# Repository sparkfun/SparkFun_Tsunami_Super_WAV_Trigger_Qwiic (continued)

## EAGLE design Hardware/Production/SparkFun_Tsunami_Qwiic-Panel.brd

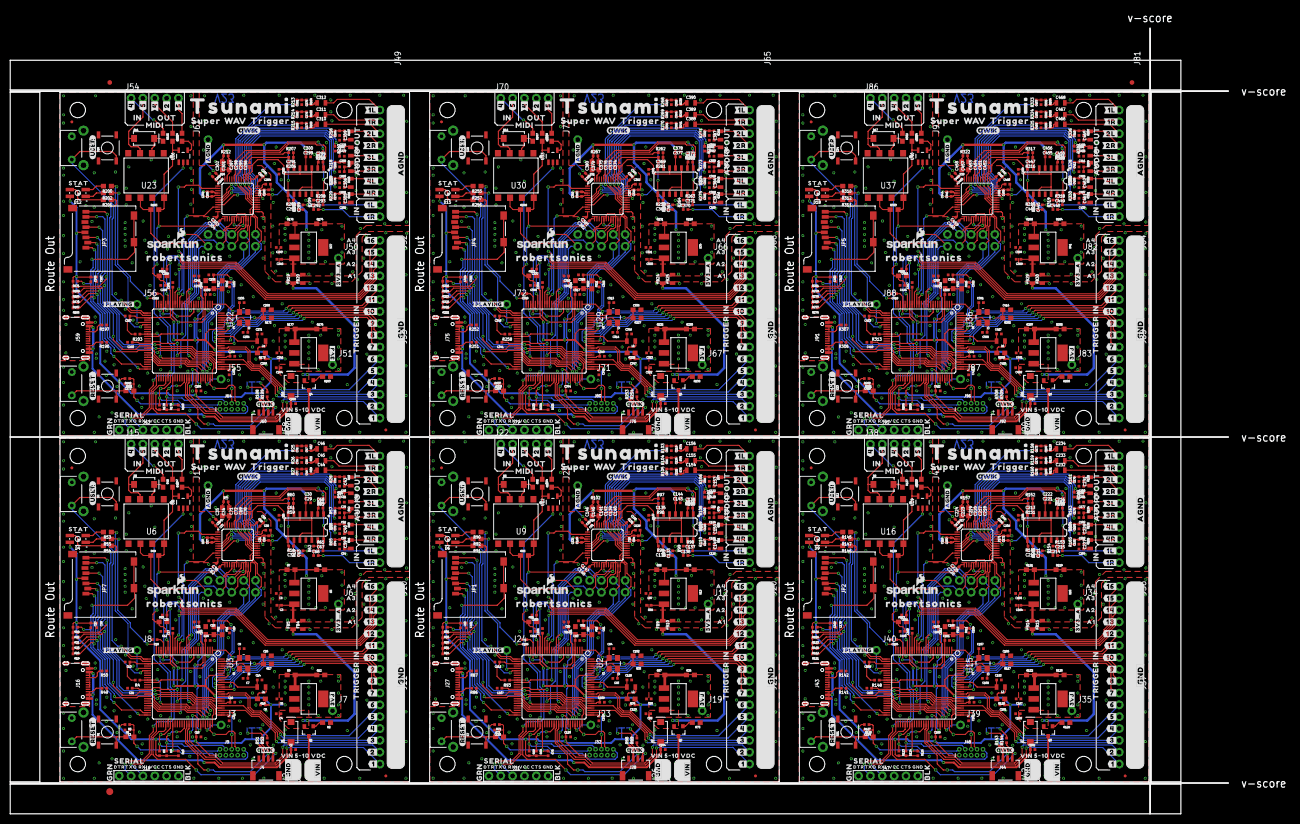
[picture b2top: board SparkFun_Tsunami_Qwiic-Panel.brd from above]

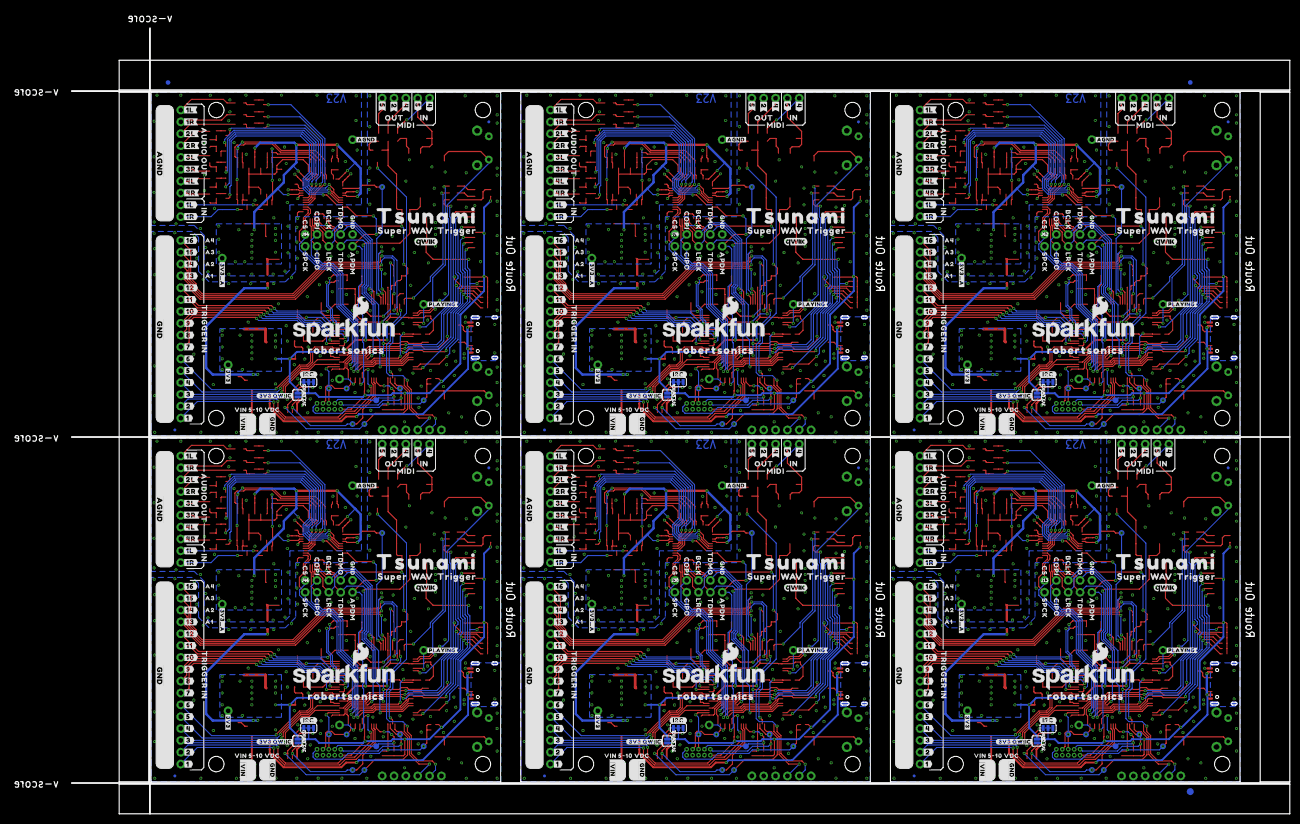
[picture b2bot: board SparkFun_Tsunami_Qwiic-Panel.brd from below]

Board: 2 copper layers, 261.1 x 168.4 mm, 1956 parts (507 on the bottom side), 828 nets.

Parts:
3V3_QWIIC, 3V3_QWIIC1, 3V3_QWIIC2, 3V3_QWIIC3, 3V3_QWIIC4, 3V3_QWIIC5: SMT-JUMPER_2_NO_SILK
C1, C116, C194, C272, C350, C428: 10nF; 0402-TIGHT
C2, C5, C6, C11, C27, C85, C87, C89, C90, C104, C163, C165, C167, C168, C182, C241, C243, C245, C246, C260, C319, C321, C323, C324, C338, C397, C399, C401, C402, C416: 10uF; 0402-TIGHT
C3, C4, C8, C10, C12, C13, C15, C16, C17, C18, C19, C21, C22, C23, C24, C26, C28, C29, C31, C36, C37, C47, C48, C49, C50, C51, C52, C53, C54, C55, C56, C57, C59, C73, C74, C75, C76, C77, C78, C79, C80, C81, C82, C83, C86, C88, C91, C93, C95, C96, C97, C98, C99, C100, C101, C103, C105, C106, C107, C108, C109, C110, C111, C112, C113, C114, C117, C118, C119, C120, C121, C122, C123, C124, C125, C126, C127, C128, C129, C131, C143, C147, C159, C160, C161, C164, C166, C169, C171, C173, C174, C175, C176, C177, C178, C179, C181, C183, C184, C185, C186, C187, C188, C189, C190, C191, C192, C195, C196, C197, C198, C199, C200, C201, C202, C203, C204, C205, C206, C207, C209, C221, C225, C237, C238, C239, C242, C244, C247, C249, C251, C252, C253, C254, C255, C256, C257, C259, C261, C262, C263, C264, C265, C266, C267, C268, C269, C270, C273, C274, C275, C276, C277, C278, C279, C280, C281, C282, C283, C284, C285, C287, C299, C303, C315, C316, C317, C320, C322, C325, C327, C329, C330, C331, C332, C333, C334, C335, C337, C339, C340, C341, C342, C343, C344, C345, C346, C347, C348, C351, C352, C353, C354, C355, C356, C357, C358, C359, C360, C361, C362, C363, C365, C377, C381, C393, C394, C395, C398, C400, C403, C405, C407, C408, C409, C410, C411, C412, C413, C415, C417, C418, C419, C420, C421, C422, C423, C424, C425, C426, C429, C430, C431, C432, C433, C434, C435, C436, C437, C438, C439, C440, C441, C443, C455, C459: 0.1uF; 0402-TIGHT
C7, C9, C64, C65, C157, C158, C235, C236, C313, C314, C391, C392: 12pF; 0402-TIGHT
C14, C115, C193, C271, C349, C427: 4.7uF; 0402-TIGHT
C20, C102, C180, C258, C336, C414: 10pF; 0603
C25, C84, C162, C240, C318, C396: 2.2uF; 0603
C30, C32, C38, C58, C60, C62, C63, C66, C69, C70, C71, C72, C92, C94, C130, C132, C133, C136, C139, C140, C141, C142, C144, C148, C170, C172, C208, C210, C211, C214, C217, C218, C219, C220, C222, C226, C248, C250, C286, C288, C289, C292, C295, C296, C297, C298, C300, C304, C326, C328, C364, C366, C367, C370, C373, C374, C375, C376, C378, C382, C404, C406, C442, C444, C445, C448, C451, C452, C453, C454, C456, C460: 1.0uF; 0402-TIGHT
C33, C61, C67, C68, C134, C135, C137, C138, C212, C213, C215, C216, C290, C291, C293, C294, C368, C369, C371, C372, C446, C447, C449, C450: 100pF; 0402-TIGHT
C34, C145, C223, C301, C379, C457: 5.6nF; 0603
C35, C146, C224, C302, C380, C458: 390nF; 0603
C39, C40, C41, C42, C43, C44, C45, C46, C149, C150, C151, C152, C153, C154, C155, C156, C227, C228, C229, C230, C231, C232, C233, C234, C305, C306, C307, C308, C309, C310, C311, C312, C383, C384, C385, C386, C387, C388, C389, C390, C461, C462, C463, C464, C465, C466, C467, C468: 22uF; 0805
D1, D2, D3, D5, D7, D8, D10, D11, D13, D14, D16, D17: 1A/40V/500mV; SMA-DIODE
D4, D6, D9, D12, D15, D18: RGB; P-LCC-4-3
E$1, E$2, E$3, E$4: FIDUCIAL-1X2
E$5, E$6: FIDUCIAL-1.5X3
FB1, FB2, FB3, FB6, FB7, FB8, FB11, FB12, FB13, FB16, FB17, FB18, FB21, FB22, FB23, FB26, FB27, FB28: 470Ω; 0603
FB4, FB5, FB9, FB10, FB14, FB15, FB19, FB20, FB24, FB25, FB29, FB30: 600Ω; 0805
FD1, FD2, FD3, FD4, FD5, FD6, FD7, FD8, FD9, FD10, FD11, FD12, FD13, FD14, FD15, FD16, FD17, FD18, FD19, FD20, FD21, FD22, FD23, FD24: FIDUCIALUFIDUCIAL; FIDUCIAL-MICRO
H1, H2, H3, H4, H5, H6, H7, H8, H9, H10, H11, H12, H13, H14, H15, H16, H17, H18, H19, H20, H21, H22, H23, H24: STAND-OFF
I2C, I2C1, I2C2, I2C3, I2C4, I2C5: SMT-JUMPER_3_2-NC_TRACE_SILK
J1, J25, J41, J57, J73, J89: VDC-IN; 1X02_NO_SILK
J2, J26, J42, J58, J74, J90: GND-IN; 1X02_NO_SILK
J3, J23, J39, J55, J71, J87: DEBUG; 1X01_NO_SILK
J4, J28, J44, J60, J76, J92: QWIIC; JST04_1MM_RA
J5, J14, J33, J49, J65, J81: AUDIO I/O; 2X10_NOSILK
J6, J12, J34, J50, J66, J82: 3.3VA; 1X01_NO_SILK
J7, J19, J35, J51, J67, J83: 3.3V; 1X01_NO_SILK
J8, J24, J40, J56, J72, J88: PLAYING; 1X01_NO_SILK
J9, J32, J48, J64, J80, J96: CORTEX_JTAG_DEBUG_PTH_NS; 2X5-PTH-1.27MM-NO_SILK
J10, J20, J36, J52, J68, J84: TRIG2; 2X8_NOSILK
J11, J21, J37, J53, J69, J85: TRIG1; 2X8_NOSILK
J13, J30, J46, J62, J78, J94: 2X5_NOSILK
J15, J22, J38, J54, J70, J86: MIDI; 1X05_NO_SILK
J16, J27, J43, J59, J75, J91: USB-C; USB-C-16P-4LAYER-ISOLATED
J17, J29, J45, J61, J77, J93: AGND; 1X01_NO_SILK
J18, J31, J47, J63, J79, J95: 6_PIN_SERIAL_TARGET_SIDE_W_SILK
JP1, JP2, JP3, JP4, JP5, JP7: USD-SOCKETNEW; MICRO-SD-SOCKET-PP
L1, L2, L3, L4, L5, L6: 10μH; 0805
LOGO1, LOGO3, LOGO5, LOGO7, LOGO9, LOGO11: QWIIC_LOGO_4MM; QWIIC_4MM
LOGO2, LOGO4, LOGO6, LOGO8, LOGO10, LOGO12: SFE_LOGO_NAME_FLAME.2_INCH; SFE_LOGO_NAME_FLAME_.2
Q1, Q2, Q3, Q4, Q5, Q6: 3.1A/30V/105mΩ; SOT23-3
R1, R71, R126, R181, R236, R291: 33; 0603
R2, R73, R128, R183, R238, R293: 1M; 0603
R3, R4, R18, R23, R31, R32, R72, R93, R115, R116, R127, R148, R170, R171, R182, R203, R225, R226, R237, R258, R280, R281, R292, R313: 10k; 0402-TIGHT
R5, R102, R157, R212, R267, R322: 560Ω; 0402-TIGHT
R6, R9, R10, R13, R19, R20, R21, R22, R24, R29, R30, R68, R69, R70, R111, R112, R113, R114, R123, R124, R125, R166, R167, R168, R169, R178, R179, R180, R221, R222, R223, R224, R233, R234, R235, R276, R277, R278, R279, R288, R289, R290: 100k; 0402-TIGHT
R7, R8, R66, R67, R121, R122, R176, R177, R231, R232, R286, R287: 390; 0603
R11, R12, R35, R36, R119, R120, R174, R175, R229, R230, R284, R285: 240; 0603
R14, R15, R59, R60, R61, R62, R63, R64, R94, R95, R96, R97, R98, R99, R100, R101, R149, R150, R151, R152, R153, R154, R155, R156, R204, R205, R206, R207, R208, R209, R210, R211, R259, R260, R261, R262, R263, R264, R265, R266, R314, R315, R316, R317, R318, R319, R320, R321: 33k; 0402-TIGHT
R16, R34, R118, R173, R228, R283: 2.2; 0603
R17, R33, R117, R172, R227, R282: 5.62k; 0603
R25, R26, R27, R28, R37, R38, R39, R40, R41, R42, R43, R44, R56, R57, R58, R65, R74, R75, R76, R77, R78, R79, R80, R81, R103, R104, R105, R106, R107, R108, R109, R110, R129, R130, R131, R132, R133, R134, R135, R136, R158, R159, R160, R161, R162, R163, R164, R165, R184, R185, R186, R187, R188, R189, R190, R191, R213, R214, R215, R216, R217, R218, R219, R220, R239, R240, R241, R242, R243, R244, R245, R246, R268, R269, R270, R271, R272, R273, R274, R275, R294, R295, R296, R297, R298, R299, R300, R301, R323, R324, R325, R326, R327, R328, R329, R330: 10Ω; 0402-TIGHT
R45, R46, R47, R48, R55, R82, R83, R84, R85, R92, R137, R138, R139, R140, R147, R192, R193, R194, R195, R202, R247, R248, R249, R250, R257, R302, R303, R304, R305, R312: 220; 0603
R49, R50, R86, R87, R141, R142, R196, R197, R251, R252, R306, R307: 5.1k; 0402-TIGHT
R51, R52, R88, R89, R143, R144, R198, R199, R253, R254, R308, R309: 2.2k; 0402-TIGHT
R53, R54, R90, R91, R145, R146, R200, R201, R255, R256, R310, R311: 100; 0603
S1, S7, S11, S15, S19, S23: Reset; TACTILE_SWITCH_SMD_5.2MM
S2, S4, S5, S6, S9, S10, S13, S14, S17, S18, S21, S22: DNP; TACTILE_SWITCH_PTH_RIGHT_ANGLE
S3, S8, S12, S16, S20, S24: User; TACTILE_SWITCH_SMD_5.2MM
TP1, TP14, TP22, TP30, TP38, TP46: I2C_SCK; PAD.03X.05
TP2, TP15, TP23, TP31, TP39, TP47: I2C_SDA; PAD.03X.05
TP3, TP5, TP17, TP25, TP33, TP41: SWDIO/TMS; PAD.03X.05
TP4, TP16, TP24, TP32, TP40, TP48: MCLK; PAD.03X.05
TP6, TP10, TP18, TP26, TP34, TP42: SWCK/TCK; PAD.03X.05
TP7, TP11, TP19, TP27, TP35, TP43: TDO; PAD.03X.05
TP8, TP12, TP20, TP28, TP36, TP44: TDI; PAD.03X.05
TP9, TP13, TP21, TP29, TP37, TP45: NRESET; PAD.03X.05
U1, U5, U13, U14, U20, U21, U27, U28, U34, U35, U41, U42: LM1117; SOT223
U2, U3, U15, U22, U29, U36: ATSAMS70N20A-AN; LQFP100
U4, U11, U18, U25, U32, U39: LMV324; SO14
U6, U9, U16, U23, U30, U37: 6N138M; 8-SMD
U7, U10, U17, U24, U31, U38: ADAU1328; LQFP-48
U8, U12, U19, U26, U33, U40: 74AHC1G125W5-7; SOT23-5
U$1, U$4, U$73, U$193, U$267, U$326, U$400, U$459, U$533, U$592, U$666, U$725: QWIIC_5MM
U$2, U$5, U$268, U$401, U$534, U$667: STAT0
U$3, U$264, U$397, U$530, U$663, U$796: GND_0
U$6, U$42, U$269, U$402, U$535, U$668: #USER#0
U$7, U$90, U$270, U$403, U$536, U$669: #RESET#0
U$8, U$9, U$100, U$101, U$271, U$272, U$404, U$405, U$537, U$538, U$670, U$671: ROBERTSONICS0
U$10, U$115, U$167, U$229, U$275, U$362, U$408, U$495, U$541, U$628, U$674, U$761: #2L#0
U$11, U$114, U$274, U$407, U$540, U$673: #1L#0
U$12, U$109, U$120, U$226, U$273, U$359, U$406, U$492, U$539, U$625, U$672, U$758: #1R#0
U$13, U$125, U$276, U$409, U$542, U$675: #2R#0
U$14, U$126, U$277, U$410, U$543, U$676: #3R#0
U$15, U$127, U$278, U$411, U$544, U$677: #3L#0
U$16, U$128, U$279, U$412, U$545, U$678: #4L#0
U$17, U$129, U$280, U$413, U$546, U$679: #4R#0
U$18, U$217, U$350, U$483, U$616, U$749: #4#3
U$19, U$218, U$351, U$484, U$617, U$750: #2#5
U$20, U$107, U$130, U$201, U$281, U$334, U$414, U$467, U$547, U$600, U$680, U$733: AUDIO_OUT0
U$21, U$46, U$108, U$123, U$131, U$157, U$202, U$207, U$282, U$307, U$335, U$340, U$415, U$440, U$468, U$473, U$548, U$573, U$601, U$606, U$681, U$706, U$734, U$739: IN0
U$22, U$106, U$132, U$200, U$283, U$333, U$416, U$466, U$549, U$599, U$682, U$732: TRIGGER_IN0
U$23, U$85, U$134, U$195, U$285, U$328, U$418, U$461, U$551, U$594, U$684, U$727: #GND#0
U$24, U$135, U$286, U$419, U$552, U$685: #1#0
U$25, U$186, U$319, U$452, U$585, U$718: SERIAL3
U$26, U$60, U$161, U$187, U$311, U$320, U$444, U$453, U$577, U$586, U$710, U$719: SUPER0
U$27, U$99, U$265, U$266, U$398, U$399, U$531, U$532, U$664, U$665, U$797, U$798: VIN_5#10_VDC0
U$28, U$84, U$133, U$194, U$284, U$327, U$417, U$460, U$550, U$593, U$683, U$726: #AGND#0
U$29, U$136, U$287, U$420, U$553, U$686: #2#0
U$30, U$137, U$288, U$421, U$554, U$687: #3#0
U$31, U$56, U$117, U$138, U$159, U$223, U$289, U$309, U$356, U$422, U$442, U$489, U$555, U$575, U$622, U$688, U$708, U$755: #4#0
U$32, U$58, U$118, U$139, U$160, U$224, U$290, U$310, U$357, U$423, U$443, U$490, U$556, U$576, U$623, U$689, U$709, U$756: #5#0
U$33, U$140, U$291, U$424, U$557, U$690: #6#0
U$34, U$142, U$292, U$425, U$558, U$691: #7#0
U$35, U$143, U$293, U$426, U$559, U$692: #8#0
U$36, U$144, U$294, U$427, U$560, U$693: #9#0
U$37, U$145, U$295, U$428, U$561, U$694: #10#0
U$38, U$146, U$296, U$429, U$562, U$695: #11#0
U$39, U$147, U$297, U$430, U$563, U$696: #12#0
U$40, U$263, U$396, U$529, U$662, U$795: #PLAYING#30
U$41, U$112, U$211, U$214, U$344, U$347, U$477, U$480, U$610, U$613, U$743, U$746: #3V3#0
U$43, U$148, U$298, U$431, U$564, U$697: #13#0
U$44, U$212, U$345, U$478, U$611, U$744: #3V3_A#0
U$45, U$122, U$156, U$206, U$306, U$339, U$439, U$472, U$572, U$605, U$705, U$738: MIDI0
U$47, U$124, U$158, U$208, U$308, U$341, U$441, U$474, U$574, U$607, U$707, U$740: OUT0
U$48, U$149, U$299, U$432, U$565, U$698: #14#0
U$49, U$150, U$300, U$433, U$566, U$699: #15#0
U$50, U$151, U$301, U$434, U$567, U$700: #16#0
U$51, U$152, U$302, U$435, U$568, U$701: A10
U$52, U$153, U$303, U$436, U$569, U$702: A20
U$53, U$154, U$304, U$437, U$570, U$703: A30
U$54, U$155, U$305, U$438, U$571, U$704: A40
U$55, U$220, U$353, U$486, U$619, U$752: #5#6
U$57, U$221, U$354, U$487, U$620, U$753: #2#6
U$59, U$222, U$355, U$488, U$621, U$754: #4#6
U$61, U$110, U$184, U$203, U$317, U$336, U$450, U$469, U$583, U$602, U$716, U$735: #GND#1
U$62, U$68, U$179, U$188, U$312, U$321, U$445, U$454, U$578, U$587, U$711, U$720: TRIGGER0
U$63, U$69, U$180, U$189, U$313, U$322, U$446, U$455, U$579, U$588, U$712, U$721: TSUNAMI0
U$64, U$70, U$181, U$190, U$314, U$323, U$447, U$456, U$580, U$589, U$713, U$722: W0
U$65, U$71, U$182, U$191, U$315, U$324, U$448, U$457, U$581, U$590, U$714, U$723: A0
U$66, U$72, U$183, U$192, U$316, U$325, U$449, U$458, U$582, U$591, U$715, U$724: V0
U$67, U$111, U$185, U$204, U$318, U$337, U$451, U$470, U$584, U$603, U$717, U$736: #VIN#2
U$74, U$235, U$368, U$501, U$634, U$767: #16#5
U$75, U$236, U$369, U$502, U$635, U$768: #15#17
U$76, U$237, U$370, U$503, U$636, U$769: #14#17
U$77, U$238, U$371, U$504, U$637, U$770: #13#17
U$78, U$239, U$372, U$505, U$638, U$771: #12#17
U$79, U$240, U$373, U$506, U$639, U$772: #11#17
U$80, U$241, U$374, U$507, U$640, U$773: #10#17
U$81, U$242, U$375, U$508, U$641, U$774: #9#17
U$82, U$243, U$376, U$509, U$642, U$775: #8#17
U$83, U$244, U$377, U$510, U$643, U$776: #7#17
U$86, U$251, U$384, U$517, U$650, U$783: CS17
U$87, U$252, U$385, U$518, U$651, U$784: BCLK19
U$88, U$253, U$386, U$519, U$652, U$785: COPI18
U$89, U$254, U$387, U$520, U$653, U$786: TDMO20
U$91, U$255, U$388, U$521, U$654, U$787: SPCK22
U$92, U$256, U$389, U$522, U$655, U$788: TDMI25
U$93, U$257, U$390, U$523, U$656, U$789: LRCK24
U$94, U$258, U$391, U$524, U$657, U$790: CIPO23
U$95, U$259, U$392, U$525, U$658, U$791: APDM26
U$96, U$260, U$393, U$526, U$659, U$792: #AGND#27
U$97, U$261, U$394, U$527, U$660, U$793: #AGND#28
U$98, U$262, U$395, U$528, U$661, U$794: #PLAYING#29
U$102, U$196, U$329, U$462, U$595, U$728: A117
U$103, U$197, U$330, U$463, U$596, U$729: A2118
U$104, U$198, U$331, U$464, U$597, U$730: A32119
U$105, U$199, U$332, U$465, U$598, U$731: A432120
U$113, U$205, U$338, U$471, U$604, U$737: #I2C#6
U$116, U$215, U$348, U$481, U$614, U$747: #1L#3
U$119, U$225, U$358, U$491, U$624, U$757: #1L#6
U$121, U$227, U$360, U$493, U$626, U$759: #1R#2
U$141, U$209, U$342, U$475, U$608, U$741: SFE_LOGO_NAME_FLAME_.1
U$162, U$213, U$346, U$479, U$612, U$745: #3V3_A#4
U$163, U$210, U$343, U$476, U$609, U$742: #3V3_QWIIC#0
U$164, U$216, U$349, U$482, U$615, U$748: #1R#3
U$165, U$219, U$352, U$485, U$618, U$751: #5#5
U$166, U$228, U$361, U$494, U$627, U$760: #1L#2
U$168, U$230, U$363, U$496, U$629, U$762: #2R#3
U$169, U$231, U$364, U$497, U$630, U$763: #3L#3
U$170, U$232, U$365, U$498, U$631, U$764: #3R#4
U$171, U$233, U$366, U$499, U$632, U$765: #4L#4
U$172, U$234, U$367, U$500, U$633, U$766: #4R#5
U$173, U$245, U$378, U$511, U$644, U$777: #6#17
U$174, U$246, U$379, U$512, U$645, U$778: #5#17
U$175, U$247, U$380, U$513, U$646, U$779: #4#17
U$176, U$248, U$381, U$514, U$647, U$780: #3#17
U$177, U$249, U$382, U$515, U$648, U$781: #2#17
U$178, U$250, U$383, U$516, U$649, U$782: #1#17
Y1, Y2, Y3, Y4, Y5, Y6: 11.2896 MHz; CRYSTAL-SMD-3.2X2.5MM_GEYER_12.60421

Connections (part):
1: D5.C, R82.2, U9.2
2: D8.C, R137.2, U16.2
3: D11.C, R192.2, U23.2
3.3V: 3V3_QWIIC.1, C6.1, C8.1, C10.1, C11.1, C12.1, C13.1, C15.1, C16.1, C27.1, C28.1, C36.1, C62.1, D4.4, FB3.1, I2C.2, J7.1, J9.1, JP7.VCC, R3.2, R4.2, R6.2, R9.2, R10.2, R12.2, R16.1, R18.2, R19.2, R20.2, R21.2, R22.2, R23.2, R47.2, R48.2, U1.2, U1.4, U3.5, U3.19, U3.28, U3.68, U3.81, U3.93, U6.8, U7.13, U8.5
3.3V1: 3V3_QWIIC1.1, C85.1, C89.1, C90.1, C101.1, C109.1, C110.1, C111.1, C112.1, C113.1, C114.1, C147.1, C148.1, D6.4, FB8.1, I2C1.2, J19.1, J32.1, JP1.VCC, R13.2, R24.2, R29.2, R30.2, R31.2, R32.2, R34.1, R36.2, R68.2, R69.2, R70.2, R72.2, R83.2, R84.2, R93.2, U2.5, U2.19, U2.28, U2.68, U2.81, U2.93, U9.8, U10.13, U12.5, U14.2, U14.4
3.3V2: 3V3_QWIIC2.1, C163.1, C167.1, C168.1, C179.1, C187.1, C188.1, C189.1, C190.1, C191.1, C192.1, C225.1, C226.1, D9.4, FB13.1, I2C2.2, J35.1, J48.1, JP2.VCC, R111.2, R112.2, R113.2, R114.2, R115.2, R116.2, R118.1, R120.2, R123.2, R124.2, R125.2, R127.2, R138.2, R139.2, R148.2, U15.5, U15.19, U15.28, U15.68, U15.81, U15.93, U16.8, U17.13, U19.5, U21.2, U21.4
3.3V3: 3V3_QWIIC3.1, C241.1, C245.1, C246.1, C257.1, C265.1, C266.1, C267.1, C268.1, C269.1, C270.1, C303.1, C304.1, D12.4, FB18.1, I2C3.2, J51.1, J64.1, JP3.VCC, R166.2, R167.2, R168.2, R169.2, R170.2, R171.2, R173.1, R175.2, R178.2, R179.2, R180.2, R182.2, R193.2, R194.2, R203.2, U22.5, U22.19, U22.28, U22.68, U22.81, U22.93, U23.8, U24.13, U26.5, U28.2, U28.4
3.3V4: 3V3_QWIIC4.1, C319.1, C323.1, C324.1, C335.1, C343.1, C344.1, C345.1, C346.1, C347.1, C348.1, C381.1, C382.1, D15.4, FB23.1, I2C4.2, J67.1, J80.1, JP4.VCC, R221.2, R222.2, R223.2, R224.2, R225.2, R226.2, R228.1, R230.2, R233.2, R234.2, R235.2, R237.2, R248.2, R249.2, R258.2, U29.5, U29.19, U29.28, U29.68, U29.81, U29.93, U30.8, U31.13, U33.5, U35.2, U35.4
3.3V5: 3V3_QWIIC5.1, C397.1, C401.1, C402.1, C413.1, C421.1, C422.1, C423.1, C424.1, C425.1, C426.1, C459.1, C460.1, D18.4, FB28.1, I2C5.2, J83.1, J96.1, JP5.VCC, R276.2, R277.2, R278.2, R279.2, R280.2, R281.2, R283.1, R285.2, R288.2, R289.2, R290.2, R292.2, R303.2, R304.2, R313.2, U36.5, U36.19, U36.28, U36.68, U36.81, U36.93, U37.8, U38.13, U40.5, U42.2, U42.4
4: D14.C, R247.2, U30.2
5: D17.C, R302.2, U37.2
56: D3.C, R45.2, U6.2
ADC1LN: C69.1, U7.40
ADC1LN1: C139.1, U10.40
ADC1LN2: C217.1, U17.40
ADC1LN3: C295.1, U24.40
ADC1LN4: C373.1, U31.40
ADC1LN5: C451.1, U38.40
ADC1LP: C70.1, U7.39
ADC1LP1: C140.1, U10.39
ADC1LP2: C218.1, U17.39
ADC1LP3: C296.1, U24.39
ADC1LP4: C374.1, U31.39
ADC1LP5: C452.1, U38.39
ADC2LN: C71.1, U7.44
ADC2LN1: C141.1, U10.44
ADC2LN2: C219.1, U17.44
ADC2LN3: C297.1, U24.44
ADC2LN4: C375.1, U31.44
ADC2LN5: C453.1, U38.44
ADC2LP: C72.1, U7.43
ADC2LP1: C142.1, U10.43
ADC2LP2: C220.1, U17.43
ADC2LP3: C298.1, U24.43
ADC2LP4: C376.1, U31.43
ADC2LP5: C454.1, U38.43
AGND: C3.2, C5.2, C29.2, C30.2, C31.2, C32.2, C37.2, C38.2, C47.2, C48.2, C49.2, C50.2, C51.2, C52.2, C53.2, C54.2, C55.2, C56.2, C57.2, C58.2, C59.2, C60.2, C73.1, C74.1, C75.1, C76.1, C77.1, C78.1, C79.1, C80.1, FB4.2, J14.2, J14.4, J14.6, J14.8, J14.10, J14.12, J14.14, J14.16, J14.18, J14.20, J17.1, R7.1, U4.11, U7.1, U7.4, U7.32, U7.34, U7.36
AGND1: C86.2, C87.2, C91.2, C92.2, C93.2, C94.2, C95.1, C96.1, C97.1, C98.1, C99.1, C100.1, C117.1, C118.1, C119.2, C120.2, C121.2, C122.2, C123.2, C124.2, C125.2, C126.2, C127.2, C128.2, C129.2, C130.2, C131.2, C132.2, C143.2, C144.2, FB10.2, J5.2, J5.4, J5.6, J5.8, J5.10, J5.12, J5.14, J5.16, J5.18, J5.20, J29.1, R66.1, U10.1, U10.4, U10.32, U10.34, U10.36, U11.11
AGND2: C164.2, C165.2, C169.2, C170.2, C171.2, C172.2, C173.1, C174.1, C175.1, C176.1, C177.1, C178.1, C195.1, C196.1, C197.2, C198.2, C199.2, C200.2, C201.2, C202.2, C203.2, C204.2, C205.2, C206.2, C207.2, C208.2, C209.2, C210.2, C221.2, C222.2, FB15.2, J33.2, J33.4, J33.6, J33.8, J33.10, J33.12, J33.14, J33.16, J33.18, J33.20, J45.1, R121.1, U17.1, U17.4, U17.32, U17.34, U17.36, U18.11
AGND3: C242.2, C243.2, C247.2, C248.2, C249.2, C250.2, C251.1, C252.1, C253.1, C254.1, C255.1, C256.1, C273.1, C274.1, C275.2, C276.2, C277.2, C278.2, C279.2, C280.2, C281.2, C282.2, C283.2, C284.2, C285.2, C286.2, C287.2, C288.2, C299.2, C300.2, FB20.2, J49.2, J49.4, J49.6, J49.8, J49.10, J49.12, J49.14, J49.16, J49.18, J49.20, J61.1, R176.1, U24.1, U24.4, U24.32, U24.34, U24.36, U25.11
AGND4: C320.2, C321.2, C325.2, C326.2, C327.2, C328.2, C329.1, C330.1, C331.1, C332.1, C333.1, C334.1, C351.1, C352.1, C353.2, C354.2, C355.2, C356.2, C357.2, C358.2, C359.2, C360.2, C361.2, C362.2, C363.2, C364.2, C365.2, C366.2, C377.2, C378.2, FB25.2, J65.2, J65.4, J65.6, J65.8, J65.10, J65.12, J65.14, J65.16, J65.18, J65.20, J77.1, R231.1, U31.1, U31.4, U31.32, U31.34, U31.36, U32.11
AGND5: C398.2, C399.2, C403.2, C404.2, C405.2, C406.2, C407.1, C408.1, C409.1, C410.1, C411.1, C412.1, C429.1, C430.1, C431.2, C432.2, C433.2, C434.2, C435.2, C436.2, C437.2, C438.2, C439.2, C440.2, C441.2, C442.2, C443.2, C444.2, C455.2, C456.2, FB30.2, J81.2, J81.4, J81.6, J81.8, J81.10, J81.12, J81.14, J81.16, J81.18, J81.20, J93.1, R286.1, U38.1, U38.4, U38.32, U38.34, U38.36, U39.11
AIN1L: C63.2, J14.17
AIN1L1: C133.2, J5.17
AIN1L2: C211.2, J33.17
AIN1L3: C289.2, J49.17
AIN1L4: C367.2, J65.17
AIN1L5: C445.2, J81.17
AIN1R: C66.2, J14.19
AIN1R1: C136.2, J5.19
AIN1R2: C214.2, J33.19
AIN1R3: C292.2, J49.19
AIN1R4: C370.2, J65.19
AIN1R5: C448.2, J81.19
AOUT1L: C46.1, C47.1, R37.2
AOUT1L1: C119.1, C156.1, R74.2
AOUT1L2: C197.1, C234.1, R129.2
AOUT1L3: C275.1, C312.1, R184.2
AOUT1L4: C353.1, C390.1, R239.2
AOUT1L5: C431.1, C468.1, R294.2
AOUT1R: C45.1, C48.1, R38.2
AOUT1R1: C120.1, C155.1, R75.2
AOUT1R2: C198.1, C233.1, R130.2
AOUT1R3: C276.1, C311.1, R185.2
AOUT1R4: C354.1, C389.1, R240.2
AOUT1R5: C432.1, C467.1, R295.2
AOUT2L: C44.2, J14.5
AOUT2L1: C154.2, J5.5
AOUT2L2: C232.2, J33.5
AOUT2L3: C310.2, J49.5
AOUT2L4: C388.2, J65.5
AOUT2L5: C466.2, J81.5
AOUT2R: C43.1, C50.1, R40.2
AOUT2R1: C122.1, C153.1, R77.2
AOUT2R2: C200.1, C231.1, R132.2
AOUT2R3: C278.1, C309.1, R187.2
AOUT2R4: C356.1, C387.1, R242.2
AOUT2R5: C434.1, C465.1, R297.2
AOUT3L: C42.2, J14.9
AOUT3L1: C152.2, J5.9
AOUT3L2: C230.2, J33.9
AOUT3L3: C308.2, J49.9
AOUT3L4: C386.2, J65.9
AOUT3L5: C464.2, J81.9
AOUT3R: C41.1, C52.1, R42.2
AOUT3R1: C124.1, C151.1, R79.2
AOUT3R2: C202.1, C229.1, R134.2
AOUT3R3: C280.1, C307.1, R189.2
AOUT3R4: C358.1, C385.1, R244.2
AOUT3R5: C436.1, C463.1, R299.2
AOUT4L: C40.1, C53.1, R43.2
AOUT4L1: C125.1, C150.1, R80.2
AOUT4L2: C203.1, C228.1, R135.2
AOUT4L3: C281.1, C306.1, R190.2
AOUT4L4: C359.1, C384.1, R245.2
AOUT4L5: C437.1, C462.1, R300.2
AOUT4R: C39.1, C54.1, R44.2
AOUT4R1: C126.1, C149.1, R81.2
AOUT4R2: C204.1, C227.1, R136.2
AOUT4R3: C282.1, C305.1, R191.2
AOUT4R4: C360.1, C383.1, R246.2
AOUT4R5: C438.1, C461.1, R301.2
APDN: J13.9, U3.70, U7.10
APDN1: J30.9, U2.70, U10.10
APDN2: J46.9, U15.70, U17.10
APDN3: J62.9, U22.70, U24.10
APDN4: J78.9, U29.70, U31.10
APDN5: J94.9, U36.70, U38.10
BCLK: J13.6, U3.11, U7.17, U7.21
BCLK1: J30.6, U2.11, U10.17, U10.21
BCLK2: J46.6, U15.11, U17.17, U17.21
BCLK3: J62.6, U22.11, U24.17, U24.21
BCLK4: J78.6, U29.11, U31.17, U31.21
BCLK5: J94.6, U36.11, U38.17, U38.21
BLUE_LED: R54.1, U3.31
BLUE_LED1: R91.1, U2.31
BLUE_LED2: R146.1, U15.31
BLUE_LED3: R201.1, U22.31
BLUE_LED4: R256.1, U29.31
BLUE_LED5: R311.1, U36.31
CC1: J16.A5, R50.2
CC2: J16.B5, R49.2
CC3: J27.B5, R86.2
CC4: J27.A5, R87.2
CC5: J43.B5, R141.2
CC6: J43.A5, R142.2
CC7: J59.B5, R196.2
CC8: J59.A5, R197.2
CC9: J75.B5, R251.2
CC10: J75.A5, R252.2
CC11: J91.B5, R306.2
CC12: J91.A5, R307.2
CM_1.5V: C55.1, U4.3, U4.5, U4.10, U4.12, U7.38
CM_1.5V1: C127.1, U10.38, U11.3, U11.5, U11.10, U11.12
CM_1.5V2: C205.1, U17.38, U18.3, U18.5, U18.10, U18.12
CM_1.5V3: C283.1, U24.38, U25.3, U25.5, U25.10, U25.12
CM_1.5V4: C361.1, U31.38, U32.3, U32.5, U32.10, U32.12
CM_1.5V5: C439.1, U38.38, U39.3, U39.5, U39.10, U39.12
DBUG: J3.1, U3.72
DBUG1: J23.1, U2.72
DBUG2: J39.1, U15.72
DBUG3: J55.1, U22.72
DBUG4: J71.1, U29.72
DBUG5: J87.1, U36.72
DGND: C1.2, C2.2, C4.2, C6.2, C7.2, C8.2, C9.2, C10.2, C11.2, C12.2, C13.2, C14.2, C15.2, C16.2, C17.2, C18.2, C19.2, C20.2, C21.2, C22.2, C23.2, C24.2, C25.2, C26.2, C27.2, C28.2, C36.2, C62.2, FB4.1, J2.1, J2.2, J4.1, J9.3, J9.5, J9.9, J10.2, J10.4, J10.6, J10.8, J10.10, J10.12, J10.14, J10.16, J11.2, J11.4, J11.6, J11.8, J11.10, J11.12, J11.14, J11.16, J13.10, J15.4, J16.GND, J16.GND2, J18.6, JP7.GND, JP7.GND1, JP7.GND3, R2.1, R8.1, R17.1, R49.1, R50.1, S1.1, S2.1, S3.1, S4.1, U3.3, U3.6, U3.7, U3.8, U3.10, U3.29, U3.67, U6.5, U7.12, U7.25, U8.1, U8.3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
DGND1: C64.2, C65.2, C81.2, C82.2, C83.2, C84.2, C85.2, C88.2, C89.2, C90.2, C101.2, C102.2, C103.2, C104.2, C105.2, C106.2, C107.2, C108.2, C109.2, C110.2, C111.2, C112.2, C113.2, C114.2, C115.2, C116.2, C147.2, C148.2, FB10.1, J20.2, J20.4, J20.6, J20.8, J20.10, J20.12, J20.14, J20.16, J21.2, J21.4, J21.6, J21.8, J21.10, J21.12, J21.14, J21.16, J22.4, J26.1, J26.2, J27.GND, J27.GND2, J28.1, J30.10, J31.6, J32.3, J32.5, J32.9, JP1.GND, JP1.GND1, JP1.GND3, R33.1, R67.1, R73.1, R86.1, R87.1, S5.1, S6.1, S7.1, S8.1, U2.3, U2.6, U2.7, U2.8, U2.10, U2.29, U2.67, U9.5, U10.12, U10.25, U12.1, U12.3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
DGND2: C157.2, C158.2, C159.2, C160.2, C161.2, C162.2, C163.2, C166.2, C167.2, C168.2, C179.2, C180.2, C181.2, C182.2, C183.2, C184.2, C185.2, C186.2, C187.2, C188.2, C189.2, C190.2, C191.2, C192.2, C193.2, C194.2, C225.2, C226.2, FB15.1, J36.2, J36.4, J36.6, J36.8, J36.10, J36.12, J36.14, J36.16, J37.2, J37.4, J37.6, J37.8, J37.10, J37.12, J37.14, J37.16, J38.4, J42.1, J42.2, J43.GND, J43.GND2, J44.1, J46.10, J47.6, J48.3, J48.5, J48.9, JP2.GND, JP2.GND1, JP2.GND3, R117.1, R122.1, R128.1, R141.1, R142.1, S9.1, S10.1, S11.1, S12.1, U15.3, U15.6, U15.7, U15.8, U15.10, U15.29, U15.67, U16.5, U17.12, U17.25, U19.1, U19.3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
DGND3: C235.2, C236.2, C237.2, C238.2, C239.2, C240.2, C241.2, C244.2, C245.2, C246.2, C257.2, C258.2, C259.2, C260.2, C261.2, C262.2, C263.2, C264.2, C265.2, C266.2, C267.2, C268.2, C269.2, C270.2, C271.2, C272.2, C303.2, C304.2, FB20.1, J52.2, J52.4, J52.6, J52.8, J52.10, J52.12, J52.14, J52.16, J53.2, J53.4, J53.6, J53.8, J53.10, J53.12, J53.14, J53.16, J54.4, J58.1, J58.2, J59.GND, J59.GND2, J60.1, J62.10, J63.6, J64.3, J64.5, J64.9, JP3.GND, JP3.GND1, JP3.GND3, R172.1, R177.1, R183.1, R196.1, R197.1, S13.1, S14.1, S15.1, S16.1, U22.3, U22.6, U22.7, U22.8, U22.10, U22.29, U22.67, U23.5, U24.12, U24.25, U26.1, U26.3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
DGND4: C313.2, C314.2, C315.2, C316.2, C317.2, C318.2, C319.2, C322.2, C323.2, C324.2, C335.2, C336.2, C337.2, C338.2, C339.2, C340.2, C341.2, C342.2, C343.2, C344.2, C345.2, C346.2, C347.2, C348.2, C349.2, C350.2, C381.2, C382.2, FB25.1, J68.2, J68.4, J68.6, J68.8, J68.10, J68.12, J68.14, J68.16, J69.2, J69.4, J69.6, J69.8, J69.10, J69.12, J69.14, J69.16, J70.4, J74.1, J74.2, J75.GND, J75.GND2, J76.1, J78.10, J79.6, J80.3, J80.5, J80.9, JP4.GND, JP4.GND1, JP4.GND3, R227.1, R232.1, R238.1, R251.1, R252.1, S17.1, S18.1, S19.1, S20.1, U29.3, U29.6, U29.7, U29.8, U29.10, U29.29, U29.67, U30.5, U31.12, U31.25, U33.1, U33.3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
DGND5: C391.2, C392.2, C393.2, C394.2, C395.2, C396.2, C397.2, C400.2, C401.2, C402.2, C413.2, C414.2, C415.2, C416.2, C417.2, C418.2, C419.2, C420.2, C421.2, C422.2, C423.2, C424.2, C425.2, C426.2, C427.2, C428.2, C459.2, C460.2, FB30.1, J84.2, J84.4, J84.6, J84.8, J84.10, J84.12, J84.14, J84.16, J85.2, J85.4, J85.6, J85.8, J85.10, J85.12, J85.14, J85.16, J86.4, J90.1, J90.2, J91.GND, J91.GND2, J92.1, J94.10, J95.6, J96.3, J96.5, J96.9, JP5.GND, JP5.GND1, JP5.GND3, R282.1, R287.1, R293.1, R306.1, R307.1, S21.1, S22.1, S23.1, S24.1, U36.3, U36.6, U36.7, U36.8, U36.10, U36.29, U36.67, U37.5, U38.12, U38.25, U40.1, U40.3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
GREEN_LED: R53.1, U3.27
GREEN_LED1: R90.1, U2.27
GREEN_LED2: R145.1, U15.27
GREEN_LED3: R200.1, U22.27
GREEN_LED4: R255.1, U29.27
GREEN_LED5: R310.1, U36.27
I2C_SCK: J4.4, R52.1, TP1.1, U3.55
I2C_SCK1: J28.4, R89.1, TP14.1, U2.55
I2C_SCK2: J44.4, R144.1, TP22.1, U15.55
I2C_SCK3: J60.4, R199.1, TP30.1, U22.55
I2C_SCK4: J76.4, R254.1, TP38.1, U29.55
I2C_SCK5: J92.4, R309.1, TP46.1, U36.55
I2C_SDA: J4.3, R51.1, TP2.1, U3.64
I2C_SDA1: J28.3, R88.1, TP15.1, U2.64
I2C_SDA2: J44.3, R143.1, TP23.1, U15.64
I2C_SDA3: J60.3, R198.1, TP31.1, U22.64
I2C_SDA4: J76.3, R253.1, TP39.1, U29.64
I2C_SDA5: J92.3, R308.1, TP47.1, U36.64
LF: C34.1, C35.1, U7.47
LF1: C145.1, C146.1, U10.47
LF2: C223.1, C224.1, U17.47
LF3: C301.1, C302.1, U24.47
LF4: C379.1, C380.1, U31.47
LF5: C457.1, C458.1, U38.47
LRCK: J13.5, U3.12, U7.18, U7.22
LRCK1: J30.5, U2.12, U10.18, U10.22
LRCK2: J46.5, U15.12, U17.18, U17.22
LRCK3: J62.5, U22.12, U24.18, U24.22
LRCK4: J78.5, U29.12, U31.18, U31.22
LRCK5: J94.5, U36.12, U38.18, U38.22
MCLK: TP4.1, U3.15, U7.2
MCLK1: TP16.1, U2.15, U10.2
MCLK2: TP24.1, U15.15, U17.2
MCLK3: TP32.1, U22.15, U24.2
MCLK4: TP40.1, U29.15, U31.2
MCLK5: TP48.1, U36.15, U38.2
MIDI-IN-PIN1: J22.1, R82.1
MIDI-IN-PIN2: D5.A, J22.2, U9.3
MIDI-IN-PIN3: J38.1, R137.1
MIDI-IN-PIN4: J15.1, R45.1
MIDI-IN-PIN5: D3.A, J15.2, U6.3
MIDI-IN-PIN6: D8.A, J38.2, U16.3
MIDI-IN-PIN7: J54.1, R192.1
MIDI-IN-PIN8: D11.A, J54.2, U23.3
MIDI-IN-PIN9: J70.1, R247.1
MIDI-IN-PIN10: D14.A, J70.2, U30.3
MIDI-IN-PIN11: J86.1, R302.1
MIDI-IN-PIN12: D17.A, J86.2, U37.3
MIDI-OUT-PIN1: J22.3, R84.1
MIDI-OUT-PIN2: J22.5, R85.2
MIDI-OUT-PIN3: J38.3, R139.1
MIDI-OUT-PIN4: J15.3, R47.1
MIDI-OUT-PIN5: J15.5, R46.2
MIDI-OUT-PIN6: J38.5, R140.2
MIDI-OUT-PIN7: J54.3, R194.1
MIDI-OUT-PIN8: J54.5, R195.2
MIDI-OUT-PIN9: J70.3, R249.1
MIDI-OUT-PIN10: J70.5, R250.2
MIDI-OUT-PIN11: J86.3, R304.1
MIDI-OUT-PIN12: J86.5, R305.2
MIN: R48.1, U3.75, U6.6
MIN1: R83.1, U2.75, U9.6
MIN2: R138.1, U15.75, U16.6
MIN3: R193.1, U22.75, U23.6
MIN4: R248.1, U29.75, U30.6
MIN5: R303.1, U36.75, U37.6
MOUT: U3.56, U8.2
MOUT1: U2.56, U12.2
MOUT2: U15.56, U19.2
MOUT3: U22.56, U26.2
MOUT4: U29.56, U33.2
MOUT5: U36.56, U40.2
unnamed: C7.1, U3.98, Y1.1
unnamed: C9.1, U3.99, Y1.3
unnamed: C19.1, FB1.1, U3.96
unnamed: C14.1, L1.2, U3.90
unnamed: C23.1, FB2.1, U3.86
unnamed: C33.2, C69.2, R14.2, R60.1, U4.8
unnamed: I2C.3, R51.2
unnamed: J8.1, U3.30
unnamed: I2C.1, R52.2
unnamed: C65.1, U2.98, Y2.1
unnamed: C34.2, R5.2
unnamed: C63.1, R15.1
unnamed: C64.1, U2.99, Y2.3
unnamed: C61.2, C70.2, R59.2, U4.7
unnamed: C68.2, C72.2, R63.2, U4.1
unnamed: C20.1, R17.2, U3.97
unnamed: C26.1, FB3.2, U3.9
unnamed: C39.2, J14.15
unnamed: C40.2, J14.13
unnamed: C41.2, J14.11
unnamed: C42.1, C51.1, R41.2
unnamed: C43.2, J14.7
unnamed: C75.2, R25.2, R37.1
unnamed: L1.1, R16.2
unnamed: R7.2, R11.1, U5.1
unnamed: R1.1, S1.3, S2.2
unnamed: C74.2, R44.1, R65.2
unnamed: C73.2, R43.1, R58.2
unnamed: R8.2, R12.1, U1.1
unnamed: C80.2, R42.1, R57.2
unnamed: C44.1, C49.1, R39.2
unnamed: C46.2, J14.1
unnamed: C45.2, J14.3
unnamed: 3V3_QWIIC.2, J4.2
unnamed: D4.2, R53.2
unnamed: D4.3, R54.2
unnamed: D4.1, R55.2
unnamed: R46.1, U8.4
unnamed: C81.1, FB6.1, U2.96
unnamed: C82.1, FB7.1, U2.86
unnamed: C102.1, R33.2, U2.97
unnamed: C103.1, FB8.2, U2.9
unnamed: C115.1, L2.2, U2.90
unnamed: L2.1, R34.2
unnamed: C3.1, FB5.2, U5.3
unnamed: R35.1, R66.2, U13.1
unnamed: R36.1, R67.2, U14.1
unnamed: C56.1, U7.35
unnamed: C61.1, R59.1, R60.2, U4.6
unnamed: R71.1, S5.2, S7.3
unnamed: C33.1, R14.1, R15.2, U4.9
unnamed: C79.2, R41.1, R56.2
unnamed: C78.2, R28.2, R40.1
unnamed: C76.2, R26.2, R38.1
unnamed: C77.2, R27.2, R39.1
unnamed: C67.2, C71.2, R61.2, R64.1, U4.14
unnamed: Q2.1, R73.2
unnamed: C66.1, R62.1
unnamed: C68.1, R63.1, R64.2, U4.2
unnamed: C67.1, R61.1, R62.2, U4.13
unnamed: C95.2, R74.1, R103.2
unnamed: C117.2, R81.1, R110.2
unnamed: C118.2, R80.1, R109.2
unnamed: C100.2, R79.1, R108.2
unnamed: C99.2, R78.1, R107.2
unnamed: C98.2, R77.1, R106.2
unnamed: C96.2, R75.1, R104.2
unnamed: C97.2, R76.1, R105.2
unnamed: R85.1, U12.4
unnamed: J24.1, U2.30
unnamed: I2C1.3, R88.2
unnamed: I2C1.1, R89.2
unnamed: D6.2, R90.2
unnamed: D6.3, R91.2
unnamed: Q1.1, R2.2
unnamed: D6.1, R92.2
unnamed: C128.1, U10.35
unnamed: C86.1, FB9.2, U13.3
unnamed: C134.2, C139.2, R94.2, R97.1, U11.8
unnamed: C133.1, R95.1
unnamed: C135.1, R96.1, R97.2, U11.6
unnamed: C134.1, R94.1, R95.2, U11.9
unnamed: C137.2, C141.2, R98.2, R101.1, U11.14
unnamed: C136.1, R99.1
unnamed: C138.1, R100.1, R101.2, U11.2
unnamed: C137.1, R98.1, R99.2, U11.13
unnamed: C145.2, R102.2
unnamed: C135.2, C140.2, R96.2, U11.7
unnamed: C138.2, C142.2, R100.2, U11.1
unnamed: 3V3_QWIIC1.2, J28.2
unnamed: C149.2, J5.15
unnamed: C150.2, J5.13
unnamed: C151.2, J5.11
unnamed: C123.1, C152.1, R78.2
unnamed: C153.2, J5.7
unnamed: C121.1, C154.1, R76.2
unnamed: C155.2, J5.3
unnamed: C156.2, J5.1
unnamed: C158.1, U15.98, Y3.1
unnamed: C157.1, U15.99, Y3.3
unnamed: C159.1, FB11.1, U15.96
unnamed: C160.1, FB12.1, U15.86
unnamed: C180.1, R117.2, U15.97
unnamed: C181.1, FB13.2, U15.9
unnamed: C193.1, L3.2, U15.90
unnamed: L3.1, R118.2
unnamed: R119.1, R121.2, U20.1
unnamed: R120.1, R122.2, U21.1
unnamed: R126.1, S9.2, S11.3
unnamed: Q3.1, R128.2
unnamed: C173.2, R129.1, R158.2
unnamed: C195.2, R136.1, R165.2
unnamed: C196.2, R135.1, R164.2
unnamed: C178.2, R134.1, R163.2
unnamed: C177.2, R133.1, R162.2
unnamed: C176.2, R132.1, R161.2
unnamed: C174.2, R130.1, R159.2
unnamed: C175.2, R131.1, R160.2
unnamed: R140.1, U19.4
unnamed: J40.1, U15.30
unnamed: I2C2.3, R143.2
unnamed: I2C2.1, R144.2
unnamed: D9.2, R145.2
unnamed: D9.3, R146.2
unnamed: D9.1, R147.2
unnamed: C206.1, U17.35
unnamed: C164.1, FB14.2, U20.3
unnamed: C212.2, C217.2, R149.2, R152.1, U18.8
unnamed: C211.1, R150.1
unnamed: C213.1, R151.1, R152.2, U18.6
unnamed: C212.1, R149.1, R150.2, U18.9
unnamed: C215.2, C219.2, R153.2, R156.1, U18.14
unnamed: C214.1, R154.1
unnamed: C216.1, R155.1, R156.2, U18.2
unnamed: C215.1, R153.1, R154.2, U18.13
unnamed: C223.2, R157.2
unnamed: C213.2, C218.2, R151.2, U18.7
unnamed: C216.2, C220.2, R155.2, U18.1
unnamed: 3V3_QWIIC2.2, J44.2
unnamed: C227.2, J33.15
unnamed: C228.2, J33.13
unnamed: C229.2, J33.11
unnamed: C201.1, C230.1, R133.2
unnamed: C231.2, J33.7
unnamed: C199.1, C232.1, R131.2
unnamed: C233.2, J33.3
unnamed: C234.2, J33.1
unnamed: C236.1, U22.98, Y4.1
unnamed: C235.1, U22.99, Y4.3
unnamed: C237.1, FB16.1, U22.96
unnamed: C238.1, FB17.1, U22.86
unnamed: C258.1, R172.2, U22.97
unnamed: C259.1, FB18.2, U22.9
unnamed: C271.1, L4.2, U22.90
unnamed: L4.1, R173.2
unnamed: R174.1, R176.2, U27.1
unnamed: R175.1, R177.2, U28.1
unnamed: R181.1, S13.2, S15.3
unnamed: Q4.1, R183.2
unnamed: C251.2, R184.1, R213.2
unnamed: C273.2, R191.1, R220.2
unnamed: C274.2, R190.1, R219.2
unnamed: C256.2, R189.1, R218.2
unnamed: C255.2, R188.1, R217.2
unnamed: C254.2, R187.1, R216.2
unnamed: C252.2, R185.1, R214.2
unnamed: C253.2, R186.1, R215.2
unnamed: R195.1, U26.4
unnamed: J56.1, U22.30
unnamed: I2C3.3, R198.2
unnamed: I2C3.1, R199.2
unnamed: D12.2, R200.2
unnamed: D12.3, R201.2
unnamed: D12.1, R202.2
unnamed: C284.1, U24.35
unnamed: C242.1, FB19.2, U27.3
unnamed: C290.2, C295.2, R204.2, R207.1, U25.8
unnamed: C289.1, R205.1
unnamed: C291.1, R206.1, R207.2, U25.6
unnamed: C290.1, R204.1, R205.2, U25.9
unnamed: C293.2, C297.2, R208.2, R211.1, U25.14
unnamed: C292.1, R209.1
unnamed: C294.1, R210.1, R211.2, U25.2
unnamed: C293.1, R208.1, R209.2, U25.13
unnamed: C301.2, R212.2
unnamed: C291.2, C296.2, R206.2, U25.7
unnamed: C294.2, C298.2, R210.2, U25.1
unnamed: 3V3_QWIIC3.2, J60.2
unnamed: C305.2, J49.15
unnamed: C306.2, J49.13
unnamed: C307.2, J49.11
unnamed: C279.1, C308.1, R188.2
unnamed: C309.2, J49.7
unnamed: C277.1, C310.1, R186.2
unnamed: C311.2, J49.3
unnamed: C312.2, J49.1
unnamed: C314.1, U29.98, Y5.1
unnamed: C313.1, U29.99, Y5.3
unnamed: C315.1, FB21.1, U29.96
unnamed: C316.1, FB22.1, U29.86
unnamed: C336.1, R227.2, U29.97
unnamed: C337.1, FB23.2, U29.9
unnamed: C349.1, L5.2, U29.90
unnamed: L5.1, R228.2
unnamed: R229.1, R231.2, U34.1
unnamed: R230.1, R232.2, U35.1
unnamed: R236.1, S17.2, S19.3
unnamed: Q5.1, R238.2
unnamed: C329.2, R239.1, R268.2
unnamed: C351.2, R246.1, R275.2
unnamed: C352.2, R245.1, R274.2
unnamed: C334.2, R244.1, R273.2
unnamed: C333.2, R243.1, R272.2
unnamed: C332.2, R242.1, R271.2
unnamed: C330.2, R240.1, R269.2
unnamed: C331.2, R241.1, R270.2
unnamed: R250.1, U33.4
unnamed: J72.1, U29.30
unnamed: I2C4.3, R253.2
unnamed: I2C4.1, R254.2
unnamed: D15.2, R255.2
unnamed: D15.3, R256.2
unnamed: D15.1, R257.2
unnamed: C362.1, U31.35
unnamed: C320.1, FB24.2, U34.3
unnamed: C368.2, C373.2, R259.2, R262.1, U32.8
unnamed: C367.1, R260.1
unnamed: C369.1, R261.1, R262.2, U32.6
unnamed: C368.1, R259.1, R260.2, U32.9
unnamed: C371.2, C375.2, R263.2, R266.1, U32.14
unnamed: C370.1, R264.1
unnamed: C372.1, R265.1, R266.2, U32.2
unnamed: C371.1, R263.1, R264.2, U32.13
unnamed: C379.2, R267.2
unnamed: C369.2, C374.2, R261.2, U32.7
unnamed: C372.2, C376.2, R265.2, U32.1
unnamed: 3V3_QWIIC4.2, J76.2
unnamed: C383.2, J65.15
unnamed: C384.2, J65.13
unnamed: C385.2, J65.11
unnamed: C357.1, C386.1, R243.2
unnamed: C387.2, J65.7
unnamed: C355.1, C388.1, R241.2
unnamed: C389.2, J65.3
unnamed: C390.2, J65.1
unnamed: C392.1, U36.98, Y6.1
unnamed: C391.1, U36.99, Y6.3
unnamed: C393.1, FB26.1, U36.96
unnamed: C394.1, FB27.1, U36.86
unnamed: C414.1, R282.2, U36.97
unnamed: C415.1, FB28.2, U36.9
unnamed: C427.1, L6.2, U36.90
unnamed: L6.1, R283.2
unnamed: R284.1, R286.2, U41.1
unnamed: R285.1, R287.2, U42.1
unnamed: R291.1, S21.2, S23.3
unnamed: Q6.1, R293.2
unnamed: C407.2, R294.1, R323.2
unnamed: C429.2, R301.1, R330.2
unnamed: C430.2, R300.1, R329.2
unnamed: C412.2, R299.1, R328.2
unnamed: C411.2, R298.1, R327.2
unnamed: C410.2, R297.1, R326.2
unnamed: C408.2, R295.1, R324.2
unnamed: C409.2, R296.1, R325.2
unnamed: R305.1, U40.4
unnamed: J88.1, U36.30
unnamed: I2C5.3, R308.2
unnamed: I2C5.1, R309.2
unnamed: D18.2, R310.2
unnamed: D18.3, R311.2
unnamed: D18.1, R312.2
unnamed: C440.1, U38.35
unnamed: C398.1, FB29.2, U41.3
unnamed: C446.2, C451.2, R314.2, R317.1, U39.8
unnamed: C445.1, R315.1
unnamed: C447.1, R316.1, R317.2, U39.6
unnamed: C446.1, R314.1, R315.2, U39.9
unnamed: C449.2, C453.2, R318.2, R321.1, U39.14
unnamed: C448.1, R319.1
unnamed: C450.1, R320.1, R321.2, U39.2
unnamed: C449.1, R318.1, R319.2, U39.13
unnamed: C457.2, R322.2
unnamed: C447.2, C452.2, R316.2, U39.7
unnamed: C450.2, C454.2, R320.2, U39.1
unnamed: 3V3_QWIIC5.2, J92.2
unnamed: C461.2, J81.15
unnamed: C462.2, J81.13
unnamed: C463.2, J81.11
unnamed: C435.1, C464.1, R298.2
unnamed: C465.2, J81.7
unnamed: C433.1, C466.1, R296.2
unnamed: C467.2, J81.3
unnamed: C468.2, J81.1
NRESET: C1.1, J9.10, R1.2, R3.1, R10.1, TP9.1, U3.58
NRESET1: C116.1, J32.10, R70.1, R71.2, R72.1, TP13.1, U2.58
NRESET2: C194.1, J48.10, R125.1, R126.2, R127.1, TP21.1, U15.58
NRESET3: C272.1, J64.10, R180.1, R181.2, R182.1, TP29.1, U22.58
NRESET4: C350.1, J80.10, R235.1, R236.2, R237.1, TP37.1, U29.58
NRESET5: C428.1, J96.10, R290.1, R291.2, R292.1, TP45.1, U36.58
OL1: R25.1, U7.28
OL2: R27.1, U7.30
OL3: R56.1, U7.6
OL4: R58.1, U7.8
OL5: R105.1, U10.30
OL6: R107.1, U10.6
OL7: R109.1, U10.8
OL8: R103.1, U10.28
OL9: R160.1, U17.30
OL10: R162.1, U17.6
OL11: R164.1, U17.8
OL12: R158.1, U17.28
OL13: R215.1, U24.30
OL14: R217.1, U24.6
OL15: R219.1, U24.8
OL16: R213.1, U24.28
OL17: R270.1, U31.30
OL18: R272.1, U31.6
OL19: R274.1, U31.8
OL20: R268.1, U31.28
OL21: R325.1, U38.30
OL22: R327.1, U38.6
OL23: R329.1, U38.8
OL24: R323.1, U38.28
OR1: R26.1, U7.29
OR2: R28.1, U7.31
OR3: R57.1, U7.7
OR4: R65.1, U7.9
OR5: R104.1, U10.29
OR6: R106.1, U10.31
OR7: R108.1, U10.7
OR8: R110.1, U10.9
OR9: R159.1, U17.29
OR10: R161.1, U17.31
OR11: R163.1, U17.7
OR12: R165.1, U17.9
OR13: R214.1, U24.29
OR14: R216.1, U24.31
OR15: R218.1, U24.7
OR16: R220.1, U24.9
OR17: R269.1, U31.29
OR18: R271.1, U31.31
OR19: R273.1, U31.7
OR20: R275.1, U31.9
OR21: R324.1, U38.29
OR22: R326.1, U38.31
OR23: R328.1, U38.7
OR24: R330.1, U38.9
RED_LED: R55.1, U3.25
RED_LED1: R92.1, U2.25
RED_LED2: R147.1, U15.25
RED_LED3: R202.1, U22.25
RED_LED4: R257.1, U29.25
RED_LED5: R312.1, U36.25
REGINPUTS: C4.1, D1.C, FB5.1, Q1.2, U1.3
REGINPUTS1: C88.1, D2.C, FB9.1, Q2.2, U14.3
REGINPUTS2: C166.1, D7.C, FB14.1, Q3.2, U21.3
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
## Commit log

2021-07-19 Bringing it all in!
2021-07-20 firmware update to fix -70dB fade bug
2021-08-03 example WAV files for Arduino Library examples
2022-02-23 Single buffer gate change
    drop in replacement for U8 single buffer IC, with new PROD_ID
2022-02-23 Update Prod_ID for U8 (buffer IC) on panel
2022-08-04 Swap 11MHz crystal for smaller package (3.2x2.5mm)
    -also bumped version in bottom copper and SCH
2022-08-23 v22 production panel
2022-10-31 Added SCH note about U3 population
    -We are now making this board with two separate SKUs. The only difference in BOM is on U3.
    -Also exported updated SCH as PDF for docs.
2023-04-06 Test points changed to larger size
    -8 test points updated. Note, these used to be the small 15mil drill hit pth/via style test points. They are now the largest SMD pad style. Note, I also kept a via in the center point of all the test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
    -Bumped version to v23 in BRD and both sheets of SCH
2023-04-06 Added reference layer circles over test points
    -for verifying against production test fixture test point position
2023-04-07 v23 production panel
